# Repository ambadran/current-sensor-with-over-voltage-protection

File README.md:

Current sensor circuit with over voltage protection.

The Voltage supported is 12<=V<=18 as this is the working range of the TL092 OpAmps used in this project.

The shunt is a 1ohm 10 watt resistor, so use current*voltage under 10watt

The overvoltage protection circuit makes sure the output is NEVER above the Vref set by 
the TL431 IC in the circuit, a potentiometer is connected for ease of setting it to 
whatever your microcontroller max Vdd (e.g 3.3v or 5v).

A single layer PCB is also designed if needed.

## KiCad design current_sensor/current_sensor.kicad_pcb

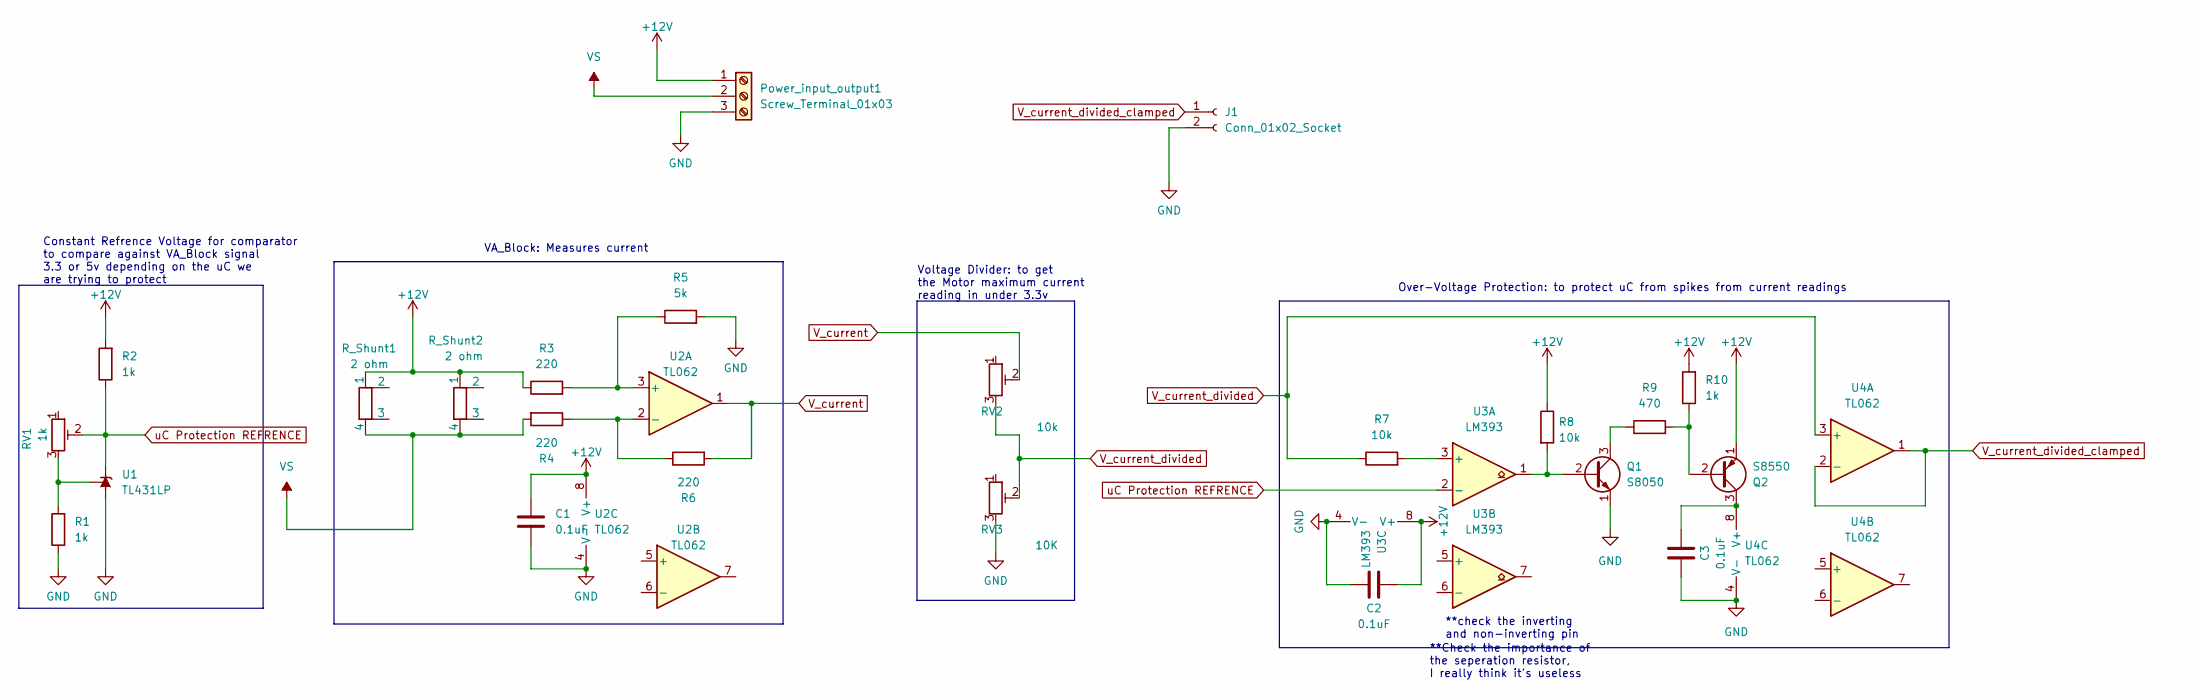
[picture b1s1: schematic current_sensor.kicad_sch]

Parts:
C1, C2, C3: 0.1uF; C_Disc_D5.0mm_W2.5mm_P5.00mm
J1: Conn_01x02_Socket; PinSocket_1x02_P2.54mm_Vertical
Power_input_output1: Screw_Terminal_01x03; TerminalBlock_bornier-3_P5.08mm
Q1: S8050; TO-92_Inline
Q2: S8550; TO-92_Inline
R1, R2, R10: 1k; R_Axial_DIN0207_L6.3mm_D2.5mm_P7.62mm_Horizontal
R3, R4, R6: 220; R_Axial_DIN0207_L6.3mm_D2.5mm_P7.62mm_Horizontal
R5: 5k; R_Axial_DIN0207_L6.3mm_D2.5mm_P7.62mm_Horizontal
R7, R8: 10k; R_Axial_DIN0207_L6.3mm_D2.5mm_P7.62mm_Horizontal
R9: 470; R_Axial_DIN0207_L6.3mm_D2.5mm_P7.62mm_Horizontal
RV1: 1k; PinSocket_1x03_P2.54mm_Vertical
RV2: 10k; PinSocket_1x03_P2.54mm_Vertical
RV3: 10K; PinSocket_1x03_P2.54mm_Vertical
R_Shunt1, R_Shunt2: 2 ohm; R_Axial_Shunt_L22.2mm_W9.5mm_PS14.30mm_P25.40mm
U1: TL431LP; TO-92_Inline
U2, U4: TL062; DIP-8_W7.62mm_Socket_LongPads
U3: LM393; DIP-8_W7.62mm_Socket_LongPads

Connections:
+12V: C1.1, C2.2, Power_input_output1.1, Q2.1 (E), R2.2, R3.1, R8.1, R10.2, R_Shunt1.1, R_Shunt2.1, U2.8 (V+), U3.8 (V+)
GND: C1.2, C2.1, C3.1, J1.2, Power_input_output1.3, Q1.1 (E), R1.1, R5.2, RV3.3, U1.2 (A), U2.4 (V-), U3.4 (V-), U4.4 (V-)
unnamed: Q1.2 (B), R8.2, U3.1
unnamed: Q1.3 (C), R9.1
unnamed: Q2.2 (B), R9.2, R10.1
unnamed: C3.2, Q2.3 (C), U4.8 (V+)
unnamed: R1.2, RV1.3, U1.1 (REF)
unnamed: R3.2, R5.1, U2.3 (+)
unnamed: R4.1, R6.1, U2.2 (-)
unnamed: R7.2, U3.3 (+)
VS: Power_input_output1.2, R4.2, R_Shunt1.4, R_Shunt2.4
V_current: R6.2, RV2.2, U2.1
V_current_divided: R7.1, RV2.3, RV3.2, U4.3 (+)
V_current_divided_clamped: J1.1, U4.1, U4.2 (-)
uC Protection REFRENCE: R2.1, RV1.2, U1.3 (K), U3.2 (-)

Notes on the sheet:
**check the inverting and non-inverting pin
Over-Voltage Protection: to protect uC from spikes from current readings
VA_Block: Measures current
Voltage Divider: to get the Motor maximum current reading in under 3.3v
Constant Refrence Voltage for comparator to compare against VA_Block signal 3.3 or 5v depending on the uC we are trying to protect
**Check the importance of the seperation resistor, I really think it's useless

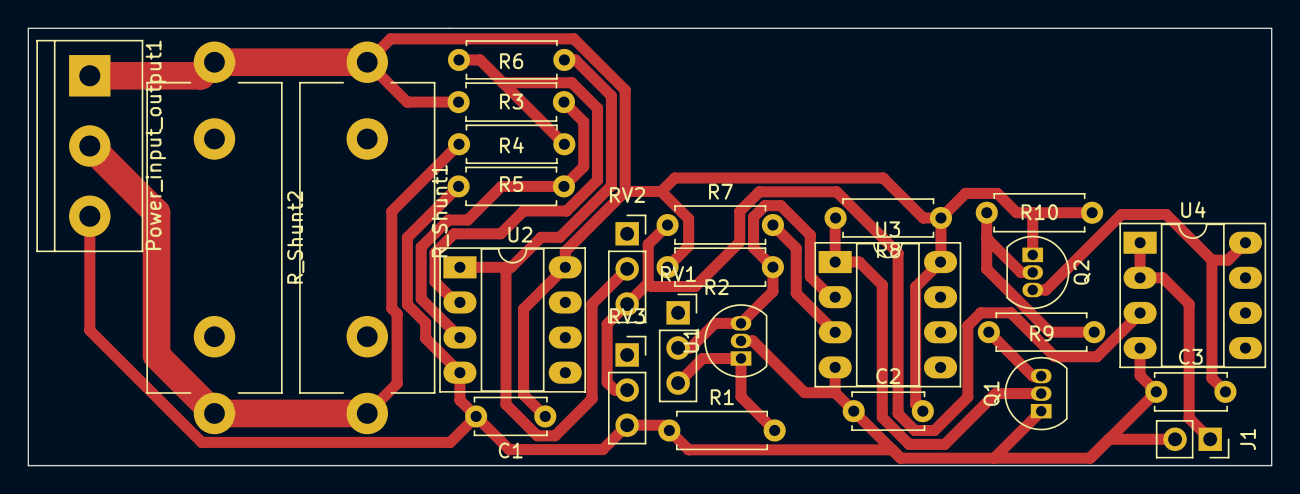
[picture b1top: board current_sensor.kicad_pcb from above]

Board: 2 copper layers, 89.9 x 31.6 mm, 26 parts (0 on the bottom side), 15 nets.

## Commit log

2023-11-02 Designed and tested schematic on breadboard
2023-11-02 Finished PCB Design
2023-11-02 minor modifications to help PCB CAM
2023-12-13 Final Version Ready
